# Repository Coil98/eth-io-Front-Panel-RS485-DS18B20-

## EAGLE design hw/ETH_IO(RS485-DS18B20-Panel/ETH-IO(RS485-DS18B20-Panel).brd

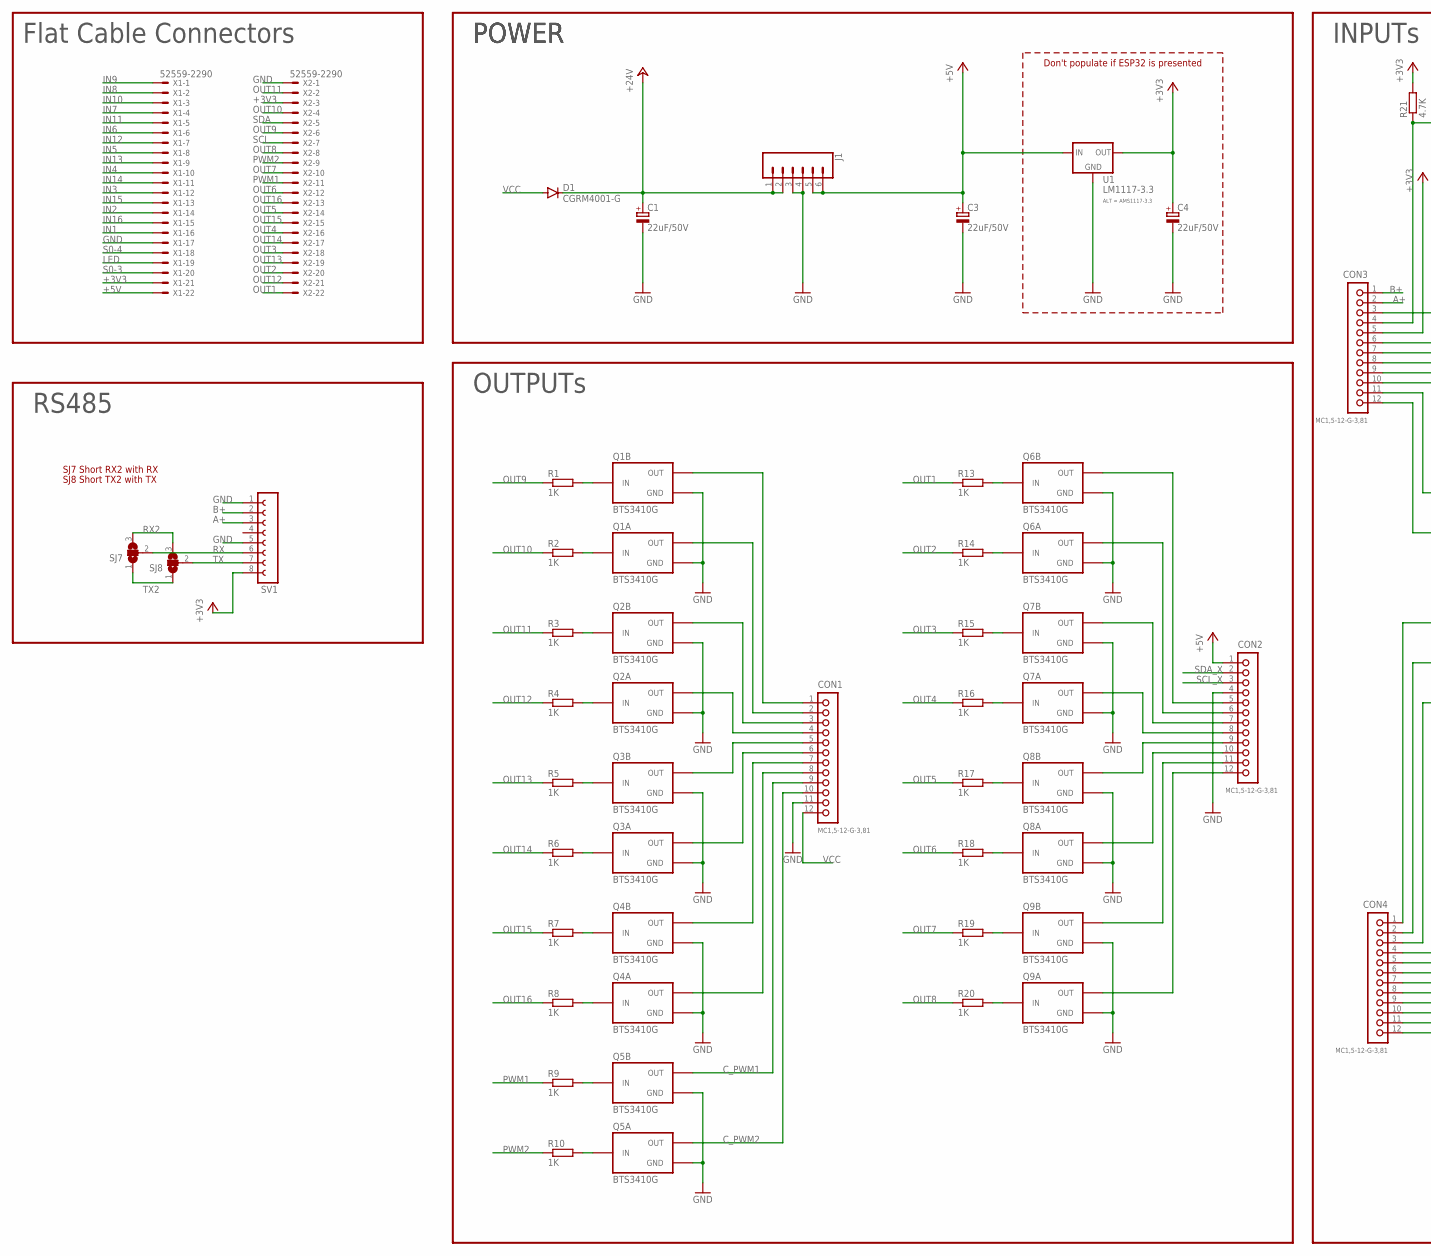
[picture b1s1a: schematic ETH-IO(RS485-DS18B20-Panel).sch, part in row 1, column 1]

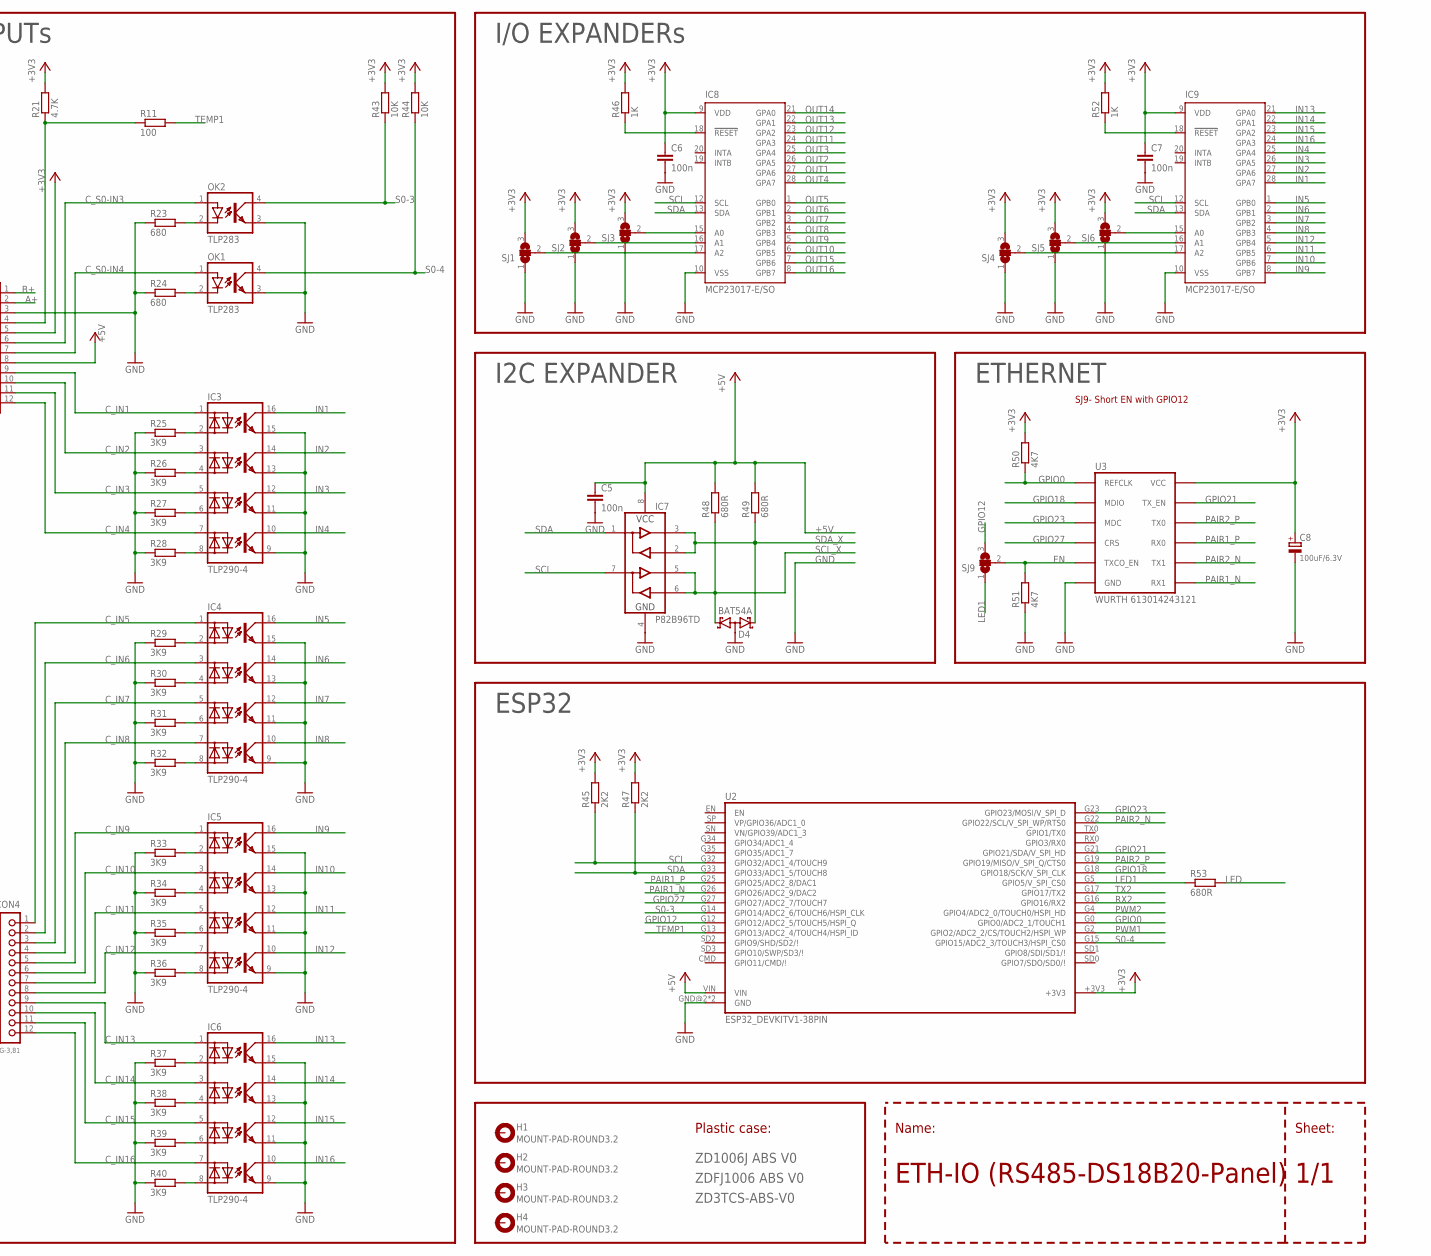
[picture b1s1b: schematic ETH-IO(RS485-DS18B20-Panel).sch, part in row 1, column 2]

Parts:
C1, C3, C4: 22uF/50V; PANASONIC_C
C5, C6, C7: 100n; C0805
C8: 100uF/6.3V; PANASONIC_C
CON1, CON2, CON3, CON4: MC1,5-12-G-3,81; MC1,5/12-G-3,81
D1: CGRM4001-G; SOD-123_MINI-SMA
D4: BAT54A; SOT23
H1, H2, H3, H4: MOUNT-PAD-ROUND3.2; 3,2-PAD
IC3, IC4, IC5, IC6: TLP290-4; SO16
IC7: P82B96TD; SO08
IC8, IC9: MCP23017-E/SO; SO28W
J1: CONN_06NO_SILK_FEMALE_PTH; 1X06_NO_SILK
OK1, OK2: TLP283; MINI-FLAT-4
Q1, Q2, Q3, Q4, Q5, Q6, Q7, Q8, Q9: BTS3410G; SO8
R1, R2, R3, R4, R5, R6, R7, R8, R9, R10, R13, R14, R15, R16, R17, R18, R19, R20, R46, R52: 1K; R0805
R11: 100; R0805
R21: 4.7K; R0805
R23, R24: 680; R0805
R25, R26, R27, R28, R29, R30, R31, R32, R33, R34, R35, R36, R37, R38, R39, R40: 3K9; R0805
R43, R44: 10K; R0805
R45, R47: 2K2; R0805
R48, R49, R53: 680R; R0805
R50, R51: 4K7; R0805
SJ1, SJ2, SJ3, SJ4, SJ5, SJ6, SJ7, SJ8, SJ9: SJ2W; SJ_2
SV1: FE08-1; FE08
U1: LM1117-3.3; SOT223
U2: ESP32_DEVKITV1-38PIN; ESP32_DEVKITV1_38PIN
U3: WURTH 613014243121; LAN8720_ETH_BOARD
X1, X2: 52559-2290

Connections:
+3V3: C4.+, C6.1, C7.1, C8.+, CON3.5, IC8.9 (VDD), IC9.9 (VDD), R21.2, R43.2, R44.2, R45.2, R46.2, R47.2, R50.2, R52.2, SJ1.3, SJ2.3, SJ3.3, SJ4.3, SJ5.3, SJ6.3, SV1.8, U1.2 (OUT), U1.4 (OUT), U2.+3V3, U3.VCC, U3.VCC@1 (VCC), X1.21, X2.3
+5V: C3.+, C5.1, CON2.1, CON3.8, IC7.8 (VCC), J1.5, J1.6, R48.2, R49.2, U1.3 (IN), U2.VIN, X1.22
+24V: C1.+, D1.C, J1.1, J1.2
A+: CON3.2, SV1.3
B+: CON3.1, SV1.2
C_IN1: CON3.9, IC3.1 (A1)
C_IN2: CON3.10, IC3.3 (A2)
C_IN3: CON3.11, IC3.5 (A3)
C_IN4: CON3.12, IC3.7 (A4)
C_IN5: CON4.1, IC4.1 (A1)
C_IN6: CON4.2, IC4.3 (A2)
C_IN7: CON4.3, IC4.5 (A3)
C_IN8: CON4.4, IC4.7 (A4)
C_IN9: CON4.5, IC5.1 (A1)
C_IN10: CON4.6, IC5.3 (A2)
C_IN11: CON4.7, IC5.5 (A3)
C_IN12: CON4.8, IC5.7 (A4)
C_IN13: CON4.9, IC6.1 (A1)
C_IN14: CON4.10, IC6.3 (A2)
C_IN15: CON4.11, IC6.5 (A3)
C_IN16: CON4.12, IC6.7 (A4)
C_OUT1: CON2.5, Q6.5 (OUT), Q6.6 (OUT)
C_OUT2: CON2.6, Q6.7 (OUT), Q6.8 (OUT)
C_OUT3: CON2.7, Q7.5 (OUT), Q7.6 (OUT)
C_OUT4: CON2.8, Q7.7 (OUT), Q7.8 (OUT)
C_OUT5: CON2.9, Q8.5 (OUT), Q8.6 (OUT)
C_OUT6: CON2.10, Q8.7 (OUT), Q8.8 (OUT)
C_OUT7: CON2.11, Q9.5 (OUT), Q9.6 (OUT)
C_OUT8: CON2.12, Q9.7 (OUT), Q9.8 (OUT)
C_OUT9: CON1.1, Q1.5 (OUT), Q1.6 (OUT)
C_OUT10: CON1.2, Q1.7 (OUT), Q1.8 (OUT)
C_OUT11: CON1.3, Q2.5 (OUT), Q2.6 (OUT)
C_OUT12: CON1.4, Q2.7 (OUT), Q2.8 (OUT)
C_OUT13: CON1.5, Q3.5 (OUT), Q3.6 (OUT)
C_OUT14: CON1.6, Q3.7 (OUT), Q3.8 (OUT)
C_OUT15: CON1.7, Q4.5 (OUT), Q4.6 (OUT)
C_OUT16: CON1.8, Q4.7 (OUT), Q4.8 (OUT)
C_PWM1: CON1.9, Q5.5 (OUT), Q5.6 (OUT)
C_PWM2: CON1.10, Q5.7 (OUT), Q5.8 (OUT)
C_S0-IN3: CON3.6, OK2.1 (A)
C_S0-IN4: CON3.7, OK1.1 (A)
EN: R51.2, SJ9.2, U3.TXCO_EN
GND: C1.-, C3.-, C4.-, C5.2, C6.2, C7.2, C8.-, CON1.11, CON2.4, CON3.3, D4.3 (AA), IC3.9 (EMIT4), IC3.11 (EMIT3), IC3.13 (EMIT2), IC3.15 (EMIT1), IC4.9 (EMIT4), IC4.11 (EMIT3), IC4.13 (EMIT2), IC4.15 (EMIT1), IC5.9 (EMIT4), IC5.11 (EMIT3), IC5.13 (EMIT2), IC5.15 (EMIT1), IC6.9 (EMIT4), IC6.11 (EMIT3), IC6.13 (EMIT2), IC6.15 (EMIT1), IC7.4 (GND), IC8.10 (VSS), IC9.10 (VSS), J1.3, J1.4, OK1.3 (EMIT), OK2.3 (EMIT), Q1.1 (GND), Q1.3 (GND), Q2.1 (GND), Q2.3 (GND), Q3.1 (GND), Q3.3 (GND), Q4.1 (GND), Q4.3 (GND), Q5.1 (GND), Q5.3 (GND), Q6.1 (GND), Q6.3 (GND), Q7.1 (GND), Q7.3 (GND), Q8.1 (GND), Q8.3 (GND), Q9.1 (GND), Q9.3 (GND), R23.1, R24.1, R25.1, R26.1, R27.1, R28.1, R29.1, R30.1, R31.1, R32.1, R33.1, R34.1, R35.1, R36.1, R37.1, R38.1, R39.1, R40.1, R51.1, SJ1.1, SJ2.1, SJ3.1, SJ4.1, SJ5.1, SJ6.1, SV1.1, SV1.5, U1.1 (GND), U2.GND@2 (GND), U2.GND@3 (GND), U3.GND, U3.GND@1 (GND), X1.17, X2.1
GPIO0: R50.1, U2.G0 (GPIO0/ADC2_1/TOUCH1), U3.INT (REFCLK)
GPIO12: SJ9.3, U2.G12 (GPIO12/ADC2_5/TOUCH5/HSPI_Q)
GPIO18: U2.G18 (GPIO18/SCK/V_SPI_CLK), U3.MDIO
GPIO21: U2.G21 (GPIO21/SDA/V_SPI_HD), U3.TX_EN
GPIO23: U2.G23 (GPIO23/MOSI/V_SPI_D), U3.MDC
GPIO27: U2.G27 (GPIO27/ADC2_7/TOUCH7), U3.CRS
IN1: IC3.16 (COL1), IC9.28 (GPA7), X1.16
IN2: IC3.14 (COL2), IC9.27 (GPA6), X1.14
IN3: IC3.12 (COL3), IC9.26 (GPA5), X1.12
IN4: IC3.10 (COL4), IC9.25 (GPA4), X1.10
IN5: IC4.16 (COL1), IC9.1 (GPB0), X1.8
IN6: IC4.14 (COL2), IC9.2 (GPB1), X1.6
IN7: IC4.12 (COL3), IC9.3 (GPB2), X1.4
IN8: IC4.10 (COL4), IC9.4 (GPB3), X1.2
IN9: IC5.16 (COL1), IC9.8 (GPB7), X1.1
IN10: IC5.14 (COL2), IC9.7 (GPB6), X1.3
IN11: IC5.12 (COL3), IC9.6 (GPB5), X1.5
IN12: IC5.10 (COL4), IC9.5 (GPB4), X1.7
IN13: IC6.16 (COL1), IC9.21 (GPA0), X1.9
IN14: IC6.14 (COL2), IC9.22 (GPA1), X1.11
IN15: IC6.12 (COL3), IC9.23 (GPA2), X1.13
IN16: IC6.10 (COL4), IC9.24 (GPA3), X1.15
LED: R53.2, X1.19
LED1: R53.1, SJ9.1, U2.G5 (GPIO5/V_SPI_CS0)
unnamed: IC9.15 (A0), SJ6.2
unnamed: IC8.16 (A1), SJ2.2
unnamed: Q1.2 (IN), R2.2
unnamed: Q1.4 (IN), R1.2
unnamed: IC8.18 (!RESET), R46.1
unnamed: IC9.18 (!RESET), R52.1
unnamed: IC8.15 (A0), SJ3.2
unnamed: Q5.4 (IN), R9.2
unnamed: Q5.2 (IN), R10.2
unnamed: IC9.16 (A1), SJ5.2
unnamed: IC3.2 (C1), R25.2
unnamed: IC3.4 (C2), R26.2
unnamed: IC3.6 (C3), R27.2
unnamed: IC3.8 (C4), R28.2
unnamed: IC4.2 (C1), R29.2
unnamed: IC4.4 (C2), R30.2
unnamed: IC4.6 (C3), R31.2
unnamed: IC4.8 (C4), R32.2
unnamed: IC5.2 (C1), R33.2
unnamed: IC5.4 (C2), R34.2
unnamed: IC5.6 (C3), R35.2
unnamed: IC5.8 (C4), R36.2
unnamed: IC6.2 (C1), R37.2
unnamed: IC6.4 (C2), R38.2
unnamed: IC6.6 (C3), R39.2
unnamed: IC6.8 (C4), R40.2
unnamed: IC9.17 (A2), SJ4.2
unnamed: Q2.4 (IN), R3.2
unnamed: Q2.2 (IN), R4.2
unnamed: IC8.17 (A2), SJ1.2
unnamed: OK2.2 (C), R23.2
unnamed: Q3.4 (IN), R5.2
unnamed: Q3.2 (IN), R6.2
unnamed: CON3.4, R11.1, R21.1
unnamed: Q4.4 (IN), R7.2
unnamed: Q4.2 (IN), R8.2
unnamed: Q6.4 (IN), R13.2
unnamed: Q6.2 (IN), R14.2
unnamed: Q7.4 (IN), R15.2
unnamed: Q7.2 (IN), R16.2
unnamed: Q8.4 (IN), R17.2
unnamed: Q8.2 (IN), R18.2
unnamed: Q9.4 (IN), R19.2
unnamed: Q9.2 (IN), R20.2
unnamed: OK1.2 (C), R24.2
OUT1: IC8.27 (GPA6), R13.1, X2.22
OUT2: IC8.26 (GPA5), R14.1, X2.20
OUT3: IC8.25 (GPA4), R15.1, X2.18
OUT4: IC8.28 (GPA7), R16.1, X2.16
OUT5: IC8.1 (GPB0), R17.1, X2.14
OUT6: IC8.2 (GPB1), R18.1, X2.12
OUT7: IC8.3 (GPB2), R19.1, X2.10
OUT8: IC8.4 (GPB3), R20.1, X2.8
OUT9: IC8.5 (GPB4), R1.1, X2.6
OUT10: IC8.6 (GPB5), R2.1, X2.4
OUT11: IC8.24 (GPA3), R3.1, X2.2
OUT12: IC8.23 (GPA2), R4.1, X2.21
OUT13: IC8.22 (GPA1), R5.1, X2.19
OUT14: IC8.21 (GPA0), R6.1, X2.17
OUT15: IC8.7 (GPB6), R7.1, X2.15
OUT16: IC8.8 (GPB7), R8.1, X2.13
PAIR1_N: U2.G26 (GPIO26/ADC2_9/DAC2), U3.RX1
PAIR1_P: U2.G25 (GPIO25/ADC2_8/DAC1), U3.RX0
PAIR2_N: U2.G22 (GPIO22/SCL/V_SPI_WP/RTS0), U3.TX1
PAIR2_P: U2.G19 (GPIO19/MISO/V_SPI_Q/CTS0), U3.TX0
PWM1: R9.1, U2.G2 (GPIO2/ADC2_2/CS/TOUCH2/HSPI_WP), X2.11
PWM2: R10.1, U2.G4 (GPIO4/ADC2_0/TOUCH0/HSPI_HD), X2.9
RX: SJ7.2, SV1.6
RX2: SJ7.3, SJ8.3, U2.G16 (GPIO16/RX2)
S0-3: OK2.4 (COL), R43.1, U2.G14 (GPIO14/ADC2_6/TOUCH6/HSPI_CLK), X1.20
S0-4: OK1.4 (COL), R44.1, U2.G15 (GPIO15/ADC2_3/TOUCH3/HSPI_CS0), X1.18
SCL: IC7.7 (SY), IC8.12 (SCL), IC9.12 (SCL), R45.1, U2.G32 (GPIO32/ADC1_4/TOUCH9), X2.7
SCL_X: CON2.3, D4.1 (K1), IC7.5 (TY), IC7.6 (RY), R48.1
SDA: IC7.1 (SX), IC8.13 (SDA), IC9.13 (SDA), R47.1, U2.G33 (GPIO33/ADC1_5/TOUCH8), X2.5
SDA_X: CON2.2, D4.2 (K2), IC7.2 (RX), IC7.3 (TX), R49.1
TEMP1: R11.2, U2.G13 (GPIO13/ADC2_4/TOUCH4/HSPI_ID)
TX: SJ8.2, SV1.7
TX2: SJ7.1, SJ8.1, U2.G17 (GPIO17/TX2)
VCC: CON1.12, D1.A

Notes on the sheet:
INPUTs
I/O EXPANDERs
OUTPUTs
POWER
I2C EXPANDER
ETHERNET
ZDFJ1006 ABS V0
ZD3TCS-ABS-V0
ZD1006J ABS V0
Don't populate if ESP32 is presented
ESP32
ETH-IO (RS485-DS18B20-Panel)
Sheet:
Name:
Plastic case:
Flat Cable Connectors
RS485
SJ9- Short EN with GPIO12
SJ7 Short RX2 with RX
SJ8 Short TX2 with TX

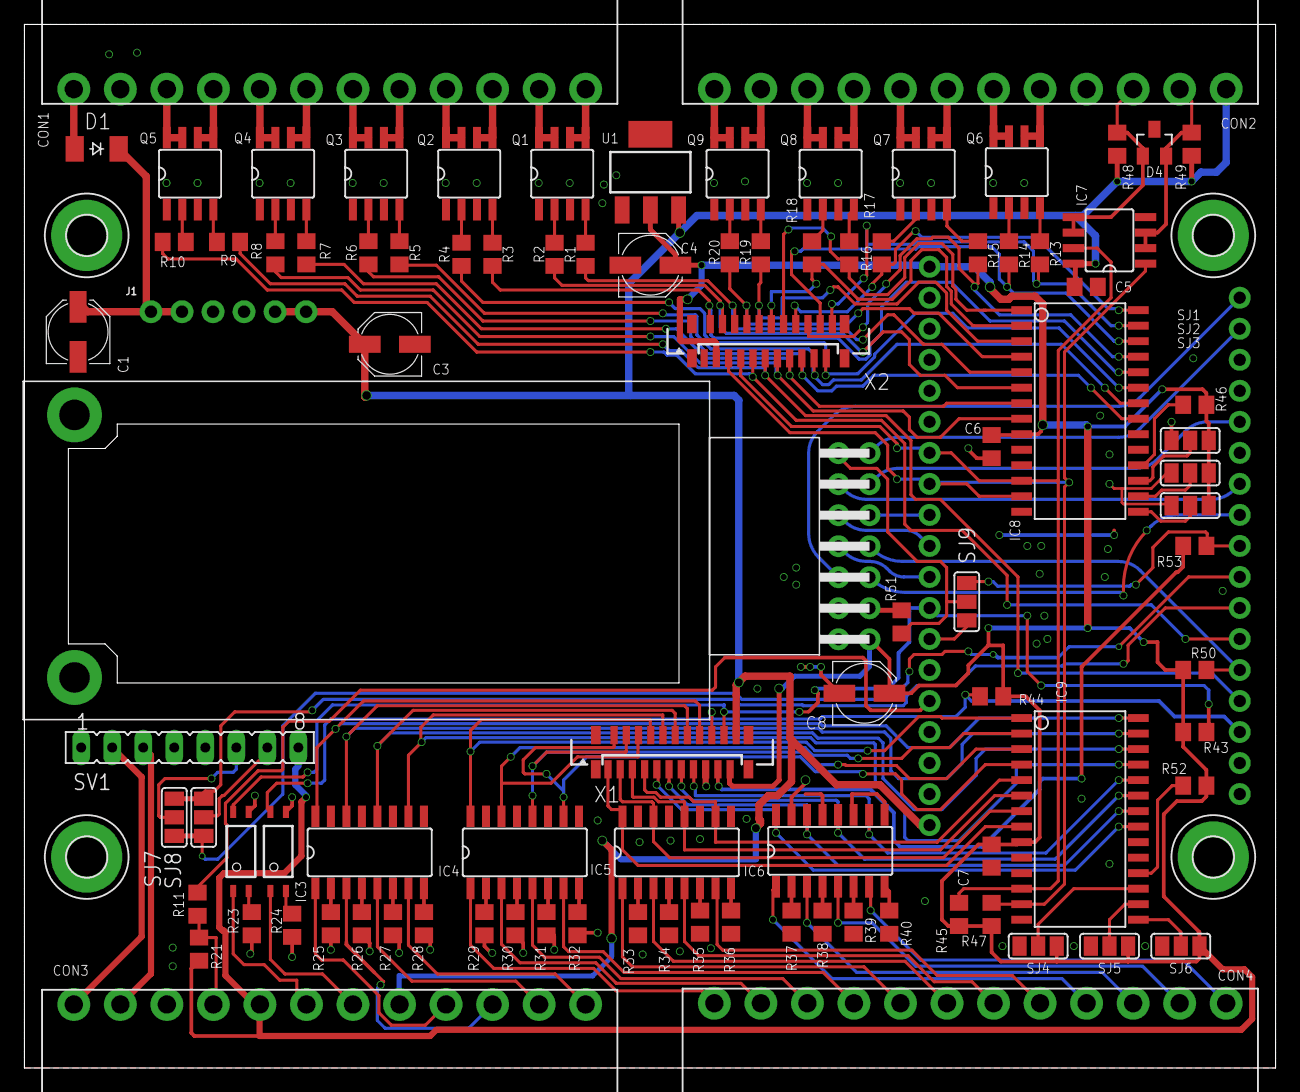
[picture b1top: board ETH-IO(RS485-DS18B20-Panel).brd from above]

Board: 2 copper layers, 102.4 x 85.4 mm, 100 parts (0 on the bottom side), 146 nets.

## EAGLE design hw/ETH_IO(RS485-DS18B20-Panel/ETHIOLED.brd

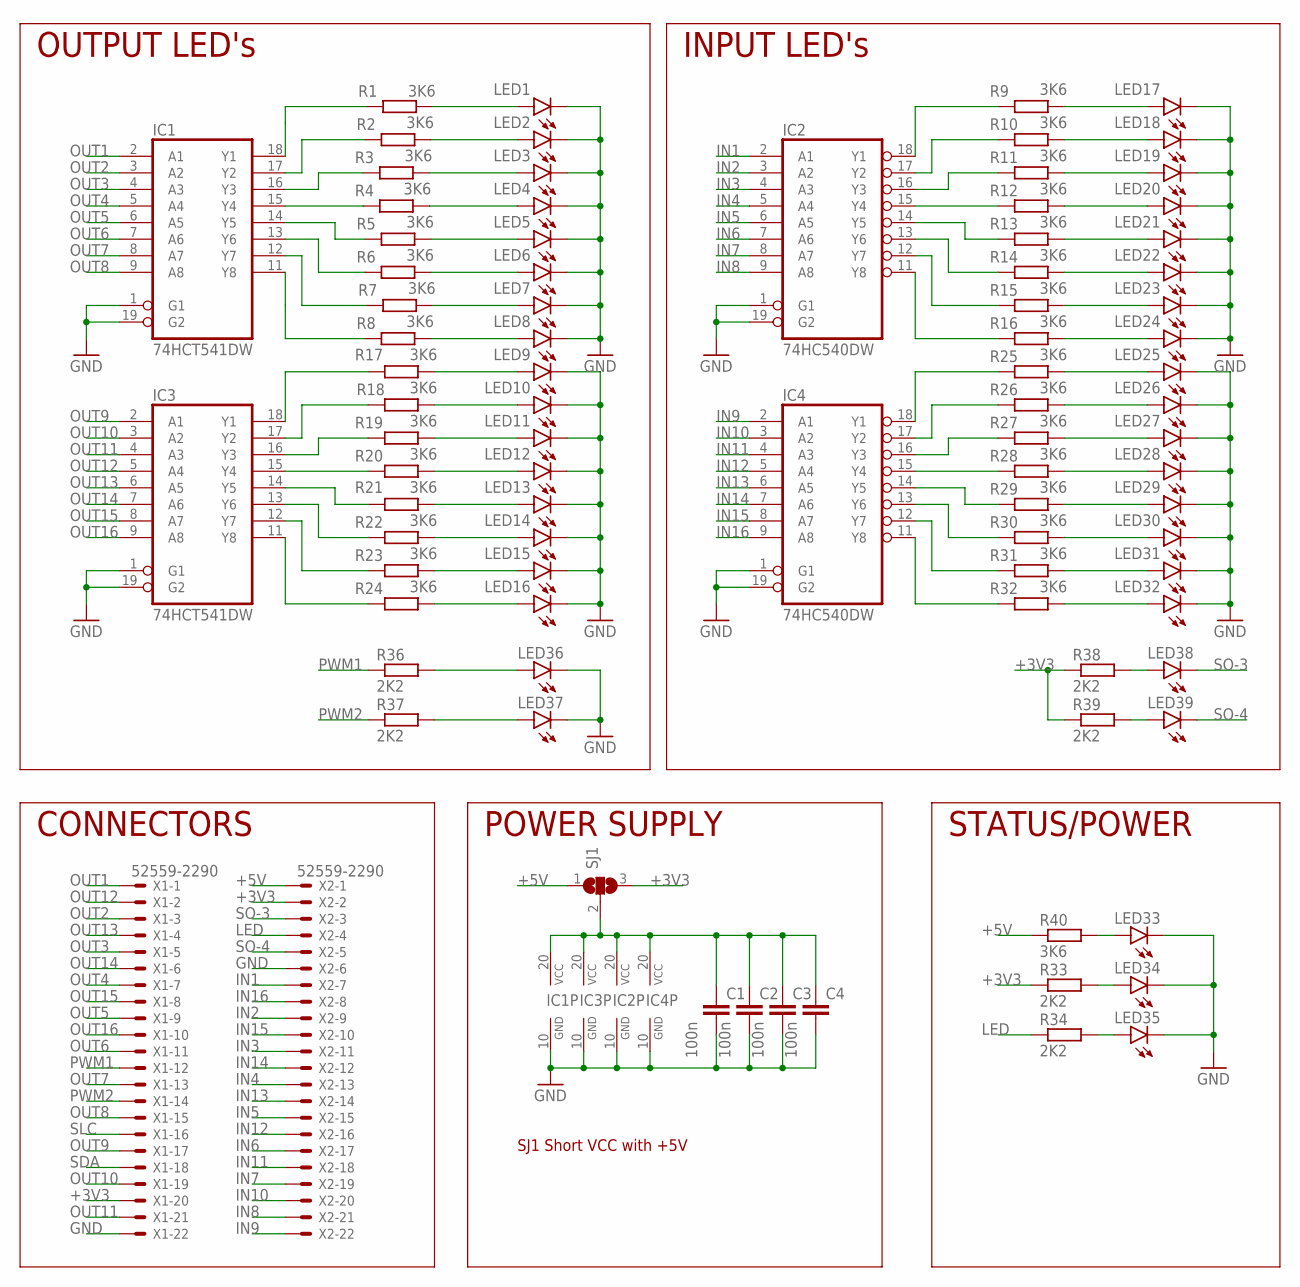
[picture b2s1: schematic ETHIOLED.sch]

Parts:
C1, C2, C3, C4: 100n; C0805
IC1, IC3: 74HCT541DW; SO20W
IC2, IC4: 74HC540DW; SO20W
LED1, LED2, LED3, LED4, LED5, LED6, LED7, LED8, LED9, LED10, LED11, LED12, LED13, LED14, LED15, LED16, LED17, LED18, LED19, LED20, LED21, LED22, LED23, LED24, LED25, LED26, LED27, LED28, LED29, LED30, LED31, LED32, LED33, LED34, LED35, LED36, LED37, LED38, LED39: LEDSML1206; SML1206
R1, R2, R3, R4, R5, R6, R7, R8, R9, R10, R11, R12, R13, R14, R15, R16, R17, R18, R19, R20, R21, R22, R23, R24, R25, R26, R27, R28, R29, R30, R31, R32: 3K6; R0805
R33, R34: 2K2; R1206
R36, R37, R38, R39: 2K2; R0805
R40: 3K6; R1206
SJ1: SJ2W; SJ_2
X1, X2: 52559-2290

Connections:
+3V3: R33.1, R38.1, R39.1, SJ1.3, X1.20, X2.2
+5V: R40.1, SJ1.1, X2.1
GND: C1.2, C2.2, C3.2, C4.2, IC1.1 (G1), IC1.10 (GND), IC1.19 (G2), IC2.1 (G1), IC2.10 (GND), IC2.19 (G2), IC3.1 (G1), IC3.10 (GND), IC3.19 (G2), IC4.1 (G1), IC4.10 (GND), IC4.19 (G2), LED1.C, LED2.C, LED3.C, LED4.C, LED5.C, LED6.C, LED7.C, LED8.C, LED9.C, LED10.C, LED11.C, LED12.C, LED13.C, LED14.C, LED15.C, LED16.C, LED17.C, LED18.C, LED19.C, LED20.C, LED21.C, LED22.C, LED23.C, LED24.C, LED25.C, LED26.C, LED27.C, LED28.C, LED29.C, LED30.C, LED31.C, LED32.C, LED33.C, LED34.C, LED35.C, LED36.C, LED37.C, X1.22, X2.6
I1: IC2.18 (Y1), R9.1
I16: IC4.11 (Y8), R32.1
IN1: IC2.2 (A1), X2.7
IN2: IC2.3 (A2), X2.9
IN3: IC2.4 (A3), X2.11
IN4: IC2.5 (A4), X2.13
IN5: IC2.6 (A5), X2.15
IN6: IC2.7 (A6), X2.17
IN7: IC2.8 (A7), X2.19
IN8: IC2.9 (A8), X2.21
IN9: IC4.2 (A1), X2.22
IN10: IC4.3 (A2), X2.20
IN11: IC4.4 (A3), X2.18
IN12: IC4.5 (A4), X2.16
IN13: IC4.6 (A5), X2.14
IN14: IC4.7 (A6), X2.12
IN15: IC4.8 (A7), X2.10
IN16: IC4.9 (A8), X2.8
LED: R34.1, X2.4
unnamed: IC3.12 (Y7), R23.1
unnamed: IC3.13 (Y6), R22.1
unnamed: IC3.14 (Y5), R21.1
unnamed: IC3.15 (Y4), R20.1
unnamed: IC3.16 (Y3), R19.1
unnamed: IC3.17 (Y2), R18.1
unnamed: IC3.18 (Y1), R17.1
unnamed: IC2.17 (Y2), R10.1
unnamed: IC2.16 (Y3), R11.1
unnamed: IC2.15 (Y4), R12.1
unnamed: IC2.14 (Y5), R13.1
unnamed: IC2.13 (Y6), R14.1
unnamed: IC2.12 (Y7), R15.1
unnamed: IC2.11 (Y8), R16.1
unnamed: IC1.11 (Y8), R8.1
unnamed: IC1.12 (Y7), R7.1
unnamed: IC1.13 (Y6), R6.1
unnamed: IC1.14 (Y5), R5.1
unnamed: IC1.15 (Y4), R4.1
unnamed: IC1.16 (Y3), R3.1
unnamed: IC1.17 (Y2), R2.1
unnamed: IC4.18 (Y1), R25.1
unnamed: IC4.17 (Y2), R26.1
unnamed: IC4.16 (Y3), R27.1
unnamed: IC4.15 (Y4), R28.1
unnamed: IC4.14 (Y5), R29.1
unnamed: IC4.13 (Y6), R30.1
unnamed: IC4.12 (Y7), R31.1
unnamed: LED1.A, R1.2
unnamed: LED2.A, R2.2
unnamed: LED3.A, R3.2
unnamed: LED4.A, R4.2
unnamed: LED5.A, R5.2
unnamed: LED6.A, R6.2
unnamed: LED7.A, R7.2
unnamed: LED8.A, R8.2
unnamed: LED36.A, R36.2
unnamed: LED37.A, R37.2
unnamed: LED9.A, R17.2
unnamed: LED10.A, R18.2
unnamed: LED11.A, R19.2
unnamed: LED12.A, R20.2
unnamed: LED13.A, R21.2
unnamed: LED14.A, R22.2
unnamed: LED15.A, R23.2
unnamed: LED16.A, R24.2
unnamed: LED17.A, R9.2
unnamed: LED18.A, R10.2
unnamed: LED19.A, R11.2
unnamed: LED20.A, R12.2
unnamed: LED21.A, R13.2
unnamed: LED22.A, R14.2
unnamed: LED23.A, R15.2
unnamed: LED24.A, R16.2
unnamed: LED25.A, R25.2
unnamed: LED26.A, R26.2
unnamed: LED27.A, R27.2
unnamed: LED28.A, R28.2
unnamed: LED29.A, R29.2
unnamed: LED30.A, R30.2
unnamed: LED31.A, R31.2
unnamed: LED32.A, R32.2
unnamed: LED33.A, R40.2
unnamed: LED34.A, R33.2
unnamed: C1.1, C2.1, C3.1, C4.1, IC1.20 (VCC), IC2.20 (VCC), IC3.20 (VCC), IC4.20 (VCC), SJ1.2
unnamed: LED35.A, R34.2
unnamed: LED38.A, R38.2
unnamed: LED39.A, R39.2
OUT1: IC1.2 (A1), X1.1
OUT2: IC1.3 (A2), X1.3
OUT3: IC1.4 (A3), X1.5
OUT4: IC1.5 (A4), X1.7
OUT5: IC1.6 (A5), X1.9
OUT6: IC1.7 (A6), X1.11
OUT7: IC1.8 (A7), X1.13
OUT8: IC1.9 (A8), X1.15
OUT9: IC3.2 (A1), X1.17
OUT10: IC3.3 (A2), X1.19
OUT11: IC3.4 (A3), X1.21
OUT12: IC3.5 (A4), X1.2
OUT13: IC3.6 (A5), X1.4
OUT14: IC3.7 (A6), X1.6
OUT15: IC3.8 (A7), X1.8
OUT16: IC3.9 (A8), X1.10
PWM1: R36.1, X1.12
PWM2: R37.1, X1.14
SDA: X1.18
SLC: X1.16
SO-3: LED38.C, X2.3
SO-4: LED39.C, X2.5
UT1: IC1.18 (Y1), R1.1
UT16: IC3.11 (Y8), R24.1

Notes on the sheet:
OUTPUT LED's
INPUT LED's
CONNECTORS
POWER SUPPLY
STATUS/POWER
SJ1 Short VCC with +5V

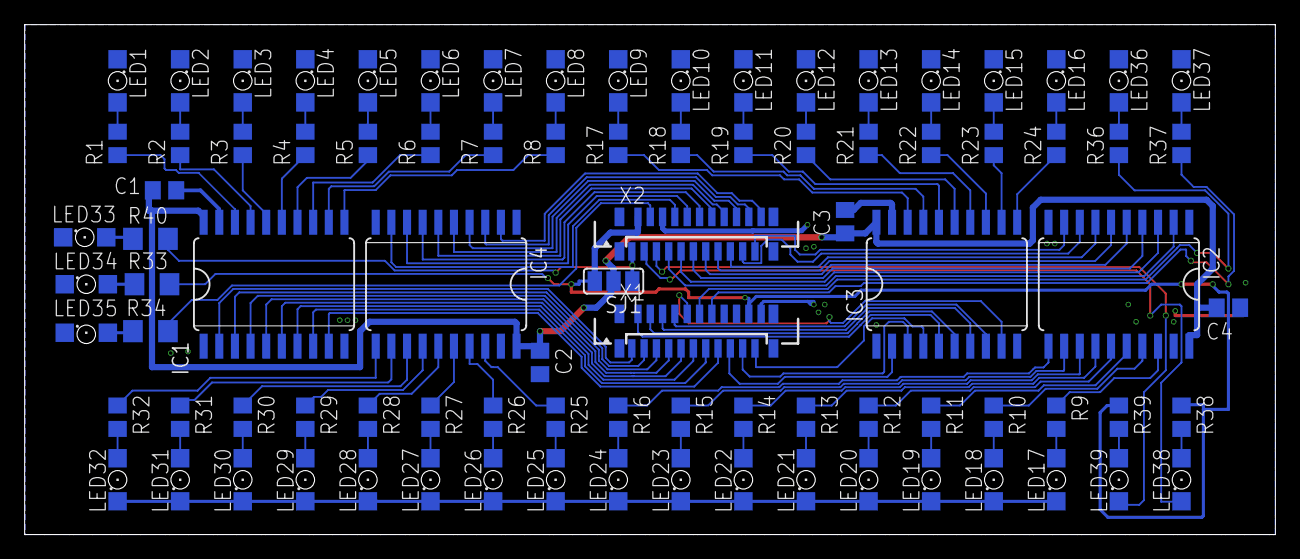
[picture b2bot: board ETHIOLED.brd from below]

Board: 2 copper layers, 101.5 x 41.4 mm, 89 parts (89 on the bottom side), 112 nets.

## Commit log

2026-01-25 add v3 PCB (#5)
    * add v3 PCB
    * bigger footprints
2026-02-23 Create placeholder

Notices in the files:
parts and their libraries:
SparkFun-Connectors: Licensing: Creative Commons ShareAlike 4.0 International - https://creativecommons.org/licenses/by-sa/4.0
